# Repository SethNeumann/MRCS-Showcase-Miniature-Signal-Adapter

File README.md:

# REPO NAME: MRCS-Showcase-Miniature-Signal-Adapter
## License: Creative Commons Attribution-NonCommercial-ShareAlike

MRCS-Showcase-Miniature-Signal-Adapter
  
Requested by Allison Dendy. The idea is to solder the mast to hole in the middle. The mast can be the common
(I'd be a little concerned if has the voltage but certainly a good idea for common-cathode signals where
the mast would be grounded). The mast and 7 other pads have holes for the signal leads and for the leads
of a CAT3, CAT5, CAT5e, CAT6 cable. Each lead has pads for an SMD resistor. the base will be buried in the 
roadbed or mounted under the layout. It could be mounted up or down as required.

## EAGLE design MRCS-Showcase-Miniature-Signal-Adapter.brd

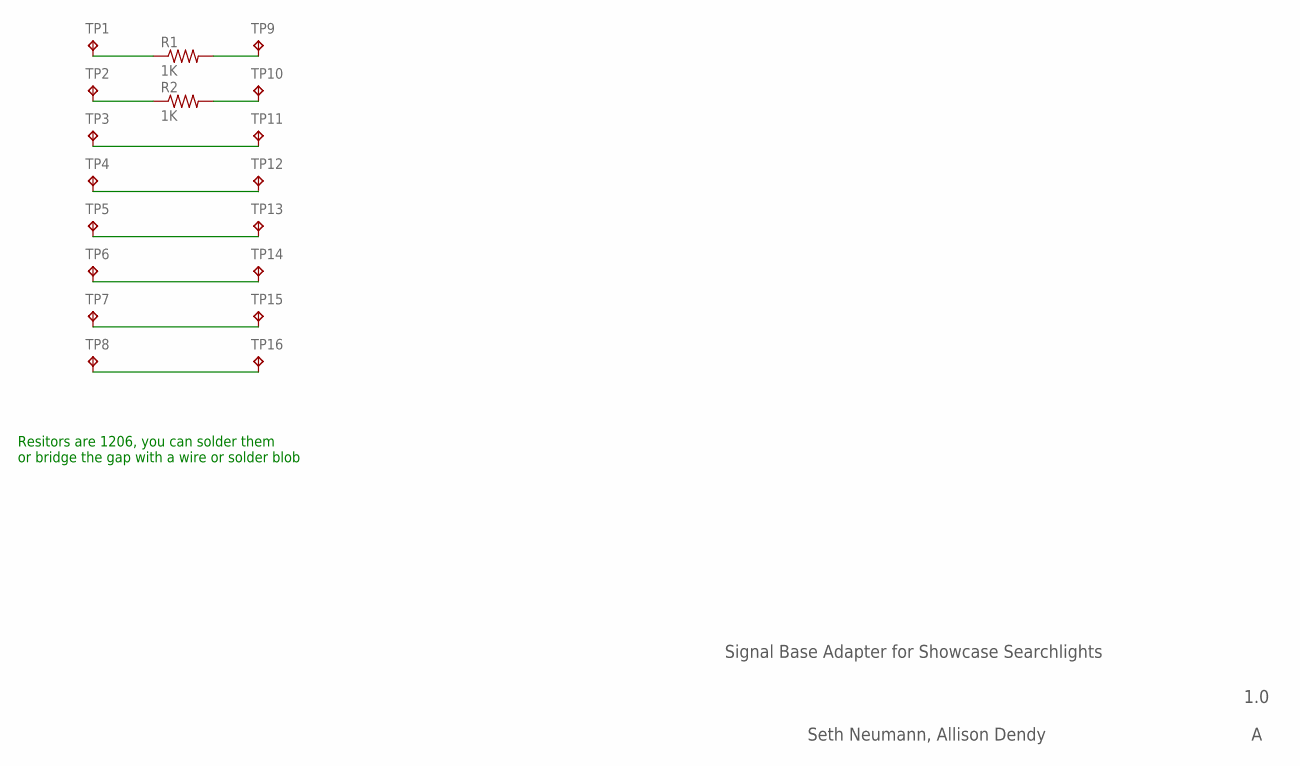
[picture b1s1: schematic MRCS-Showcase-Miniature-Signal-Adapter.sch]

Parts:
R1, R2: 1K; 1206-RES
TP1, TP2, TP3, TP4, TP5, TP6, TP7, TP8, TP9, TP10, TP11, TP12, TP13, TP14, TP15, TP16: TP; P1-06

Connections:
unnamed: R1.1, TP1.P$1
unnamed: R2.1, TP2.P$1
unnamed: R2.2, TP10.P$1
unnamed: TP3.P$1, TP11.P$1
unnamed: TP4.P$1, TP12.P$1
unnamed: TP5.P$1, TP13.P$1
unnamed: TP6.P$1, TP14.P$1
unnamed: TP7.P$1, TP15.P$1
unnamed: TP8.P$1, TP16.P$1
unnamed: R1.2, TP9.P$1

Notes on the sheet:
Signal Base Adapter for Showcase Searchlights
1.0
Seth Neumann, Allison Dendy
Resitors are 1206, you can solder them or bridge the gap with a wire or solder blob

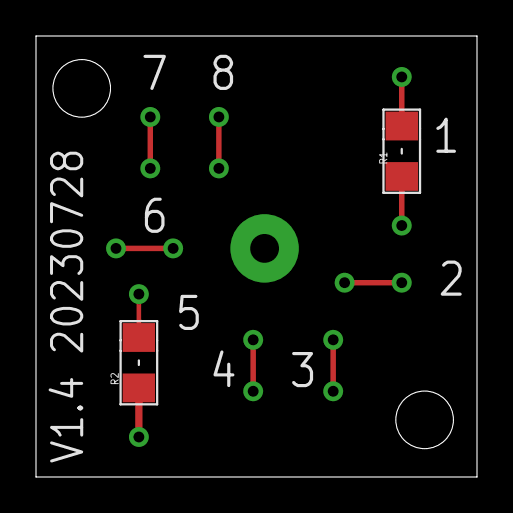
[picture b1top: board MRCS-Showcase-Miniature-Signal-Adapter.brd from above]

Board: 2 copper layers, 24.5 x 24.5 mm, 19 parts (0 on the bottom side), 10 nets.

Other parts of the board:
U$1: MRCSLOGOTOP

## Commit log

2023-05-08 initial commit
    Base with pads for smt resistors and hole for mast. Has pads for 8 wires contemplating CAT5 wire.
2023-05-08 Initial Commit
    setting up the repository
2023-05-08 Initial Commit
    setting up repository
2023-05-08 creating the sch and brd files
    creating the sch and brd files
2023-06-29 Various adjustments of hole and chip sizes
    - changed SMD resistors to 1206 to allow easier soldering
    - Changed size of shaft hole to match #52 drill
    - changes pads to .6mm for better fit with #24 wire
2023-06-29 Update INFO
    various changes in hole and resistor sizes
2023-08-08 First production version
    Showcase miniature signal base for 1 or 2 head signal, requested by Allison Dendy
2023-08-08 changed status to production
    changed status to production, panelize 4x4
2023-08-08 removing development cruft
